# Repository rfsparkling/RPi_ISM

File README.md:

# RPi ISM — open sub-GHz radio HATs for Raspberry Pi

<p align="center"><sub>RPi ISM v1 (rev 0V3) on a Raspberry Pi 3 Model B with an 868 MHz antenna on the vertical SMA. HAT rendered from the PCB data (work-in-progress layout); the Raspberry Pi is a simplified mechanical mock-up.</sub></p>

**RPi ISM** is a family of fully open radio add-on boards for the Raspberry Pi.
Hardware, firmware and software are all open source. The goal: turn any
Raspberry Pi into a capable, well-engineered sub-GHz ISM gateway, sensor hub
and RF lab tool, without proprietary hubs or closed binary stacks.

The mechanical concept, a cross-PCB receptacle that sits directly on the
Raspberry Pi GPIO header, comes from the author's
[QRPi WSPR transmitter](https://web.tapr.org/meetings/DCC_2015/DCC2015-QRPi-HA7DCD-1.pdf)
(HA7DCD), used on the Raspberry Pi 1 and 2 and produced in thousands of units
by [TAPR](https://tapr.org/product/wspr/).

<p align="center"><sub>QRPi on a Raspberry Pi 1 Model B: cross-PCB receptacle on the GPIO header, board cut-out clearing the DSI (S2) connector.</sub></p>

The first member of the family, **RPi ISM v1**, is built around the Silicon Labs
**Si4463** transceiver for the **863–870 MHz (SRD 868)** band. More families
with newer radio chips are planned (see [Product family](#product-family)).

> **Status:** early development. The v1 schematic (rev 0V3) is near-final;
> the PCB layout is being completed and migrated from Eagle to KiCad.
> The software stack is being designed. Not ready for production use yet.

---

## What is it good for?

RPi ISM v1 is an **(G)FSK / OOK** radio. It does *not* speak Zigbee, Thread or
other 2.4 GHz 802.15.4 protocols. It targets the things a cheap 2.4 GHz
dongle cannot do:

| Use case | Who | Notes |
|---|---|---|
| **Wireless M-Bus / OMS meter reading** (EN 13757-4, S1/T1/C1 modes) | Utilities, building management, home users | Water, heat, gas meters and heat-cost allocators. Planned as a [wmbusmeters](https://github.com/wmbusmeters/wmbusmeters) backend, with transmit capability. |
| **868 MHz home automation** | Home Assistant / FHEM / openHAB users | KNX-RF, eQ-3 MAX!, Homematic (classic) and other 868 MHz FSK systems. |
| **Long-range telemetry** | Industrial, agriculture, off-grid | Up to +20 dBm; the 869.40–869.65 MHz sub-band allows 500 mW ERP at 10 % duty cycle. Reaches outbuildings and basements where 2.4 GHz meshes struggle. |
| **RF pre-compliance and lab tool** | Hardware developers, test labs | CW and PN9 test signals, RSSI sweep, band occupancy and duty-cycle monitoring, LBT testing for ETSI EN 300 220. |
| **6LoWPAN / IPv6 over sub-GHz** | Researchers, makers | Through a planned Linux `mac802154` driver (802.15.4g SUN-FSK PHY). |

---

## Hardware — RPi ISM v1 (rev 0V3)

| Item | Part | Notes |
|---|---|---|
| Transceiver | Silicon Labs **Si4463-B1B-FMR** | 119–1050 MHz, (G)FSK/4(G)FSK/OOK, up to +20 dBm. [Datasheet](https://www.silabs.com/documents/public/data-sheets/Si4464-63-61-60.pdf). Moving to **Si4463-C2A** in the next revision. |
| RF filter | TDK/EPCOS **B39871B3725U410** SAW | 869 MHz. This filter fixes the board to the 868 MHz SRD band. [Datasheet](http://www.mouser.com/ds/2/400/B3725-525464.pdf) |
| RF switch | CEL **UPG2214TB-A** | TX/RX switching. [Datasheet](http://www.cel.com/pdf/datasheets/upg2214tb.pdf) |
| Reference | Kyocera **KT2520F26000ACW18TAN** TCXO | 26 MHz. [Datasheet](http://www.mouser.com/ds/2/40/kt2520_gps_e_2012-838160.pdf) |
| Antenna port | Vertical SMA (SMA1) | Population option; 50 Ω |
| Host interface | SPI + GPIO IRQ | 2×15 receptacle (Samtec CLH-115), mates with pins 1–30 of the Raspberry Pi GPIO header (SPI0 included) |
| Extras | Buzzer (BC817 driver), status LEDs | |
| PCB | 2 layers, 45.1 × 34.1 mm | |

Design files are in [`CAD/`](CAD/) (Eagle 6.4, with PDF exports of the
schematic and both copper layers).

### Known issues in rev 0V3

- PCB layout is not finished yet (unrouted nets, components outside the board outline).
- Missing flyback diode across the inductive buzzer load on the BC817 collector.
- TCXO `VC` pin floats through SJ7 (fine for the non-VC KT2520 variant only).
- The matching network is tuned for 868 MHz; other bands need new values.
- The SAW filter and the RF switch are not stocked at LCSC (relevant for JLCPCB assembly).
- The board cut-out (for the display flex) has one distorted corner arc: the top
  edge ends at x = 40.42 mm instead of 40.17 mm.

### Planned for the next revision

- KiCad migration, finished layout, JLCPCB-ready fabrication and assembly files (Gerber, BOM, CPL).
- **Band variants** via BOM options: 433 MHz, 868 MHz, 915 MHz (SAW filter and matching network change).
- Si4463-C2A silicon, the fixes listed above.

---

## Software stack (planned)

```
┌──────────────────────────────────────────────────────────────┐
│ Applications: Home Assistant · MQTT · wmbusmeters · FHEM      │
├───────────────┬──────────────────┬───────────────────────────┤
│ wM-Bus backend│ si446x-cli tools │ Linux mac802154 driver     │
│ (S/T/C modes) │ CW·PN9·RSSI scan │ → 6LoWPAN / IPv6 (wpan)    │
├───────────────┴──────────────────┴───────────────────────────┤
│ libsi446x — portable C driver (clean-room, permissive license)│
├──────────────────────────────────────────────────────────────┤
│ Linux backend: spidev + libgpiod v2  │ HAL for Zephyr / bare  │
└──────────────────────────────────────────────────────────────┘
```

1. **libsi446x** — a clean-room driver written from Silicon Labs' public API
   documentation (AN625). Portable HAL; the first backend is Linux userspace
   (`spidev` + `libgpiod`).
2. **si446x-cli** — test and bring-up tool: CW / PN9 transmit, RSSI sweep,
   packet TX/RX, band occupancy and duty-cycle logging.
3. **Wireless M-Bus** — S1/T1/C1 reception and transmission, with 3-of-6 and
   Manchester decoding in software, integrated as a wmbusmeters backend.
4. **Linux `mac802154` driver** — native 802.15.4g SUN-FSK support for
   `wpan-tools` and 6LoWPAN, aimed at upstream inclusion.
5. **Stretch goals** — DASH7 (reusing the Si4460 PHY driver of the
   Apache-2.0 [Sub-IoT / OSS-7](https://github.com/CoSys-Lab/dash7-ap-open-source-stack)
   stack); a Wi-SUN radio co-processor compatible with Silicon Labs'
   [wisun-br-linux](https://github.com/SiliconLabs/wisun-br-linux) border router.

**Timing note:** at 100 kbps (wM-Bus C1) the 64-byte FIFO (129 bytes when
merged) fills in about 5–10 ms, which a userspace IRQ handler can serve.
Long T1 telegrams and 6LoWPAN at higher rates are better served by the
kernel driver or a PREEMPT_RT kernel.

---

## Product family

RPi ISM v1 is the first board of a family. The shared parts — the
Raspberry Pi mechanical and electrical interface, the Linux integration,
the test tools and the open, clean-room software policy — carry over to
every member. Each new board adds a radio.

| Family | Radio | Bands / protocols | Status |
|---|---|---|---|
| **RPi ISM v1** | Si4463 | Sub-GHz (G)FSK/OOK: wM-Bus, KNX-RF, proprietary FSK, 802.15.4g | Layout in progress |
| **[ionos-maximus](https://github.com/ionos-sdr/ionos-maximus-rpi-sdr)** | EFR32FG23 (Silabs radio board BRD4265B) | Sub-GHz packet modem **and** I/Q streaming to the Pi (target ~1 Msps) | Routed, first board to be completed |
| Next generations | Newer sub-GHz and multi-protocol radios | Candidates: LoRa + FSK, Wi-SUN-class sub-GHz, dual-radio boards adding 2.4 GHz (Zigbee / Thread RCP) next to sub-GHz | Planned |

Where the family is most useful in industry, and how that sets the software
roadmap: [docs/industrial-use-cases.md](docs/industrial-use-cases.md).

Chip selection for the next families is open. Suggestions and use cases are
welcome in the issues.

---

## Licensing and clean-room policy

- **Hardware** (schematics, layouts, fabrication files, 3D and mechanical
  files): [**CERN-OHL-S-2.0**](LICENSES/CERN-OHL-S-2.0.txt).
- **Software and firmware** (drivers, libraries, tools):
  [**Apache-2.0**](LICENSES/Apache-2.0.txt), so the driver can be built into
  commercial products as well.
- Details in [`LICENSE`](LICENSE). Earlier revisions were published under the
  GPL v3 and remain available under it.
- **No code under the Silicon Labs Master Software License Agreement (MSLA)
  is included.** The MSLA is the default license of the Gecko SDK and is
  not an open source license.
- Silicon Labs files that are explicitly marked **Zlib** in their header may
  be reused, with the license notice kept and modifications clearly marked.
- Radio configurations are written from the public datasheet and API
  documentation. Binary ROM patches are not redistributed.
- Third-party code with copyleft licenses (for example RadioHead, GPL) is
  only used where license compatibility is confirmed.

---

## Repository layout

```
CAD/         Eagle design files (schematic, board) and PDF exports — rev 0V3
datasheet/   Links to component datasheets and Raspberry Pi interfacing docs
docs/img/    Renders and photos
LICENSES/    Full license texts (CERN-OHL-S-2.0, Apache-2.0)
RPism_buzzer_crossreference_file.xlsx   Raspberry Pi J8 ↔ radio pin mapping
top.png      Layout preview
```

KiCad sources, firmware and software directories will be added as the work
progresses.

---

## Contributing

Issues and pull requests are welcome: hardware review, protocol support,
band variants and real-world test results are all valuable. For larger
changes, open an issue first to discuss the approach.

Developed by **RF Sparkling Kft.** (Budapest / Veszprém, Hungary).

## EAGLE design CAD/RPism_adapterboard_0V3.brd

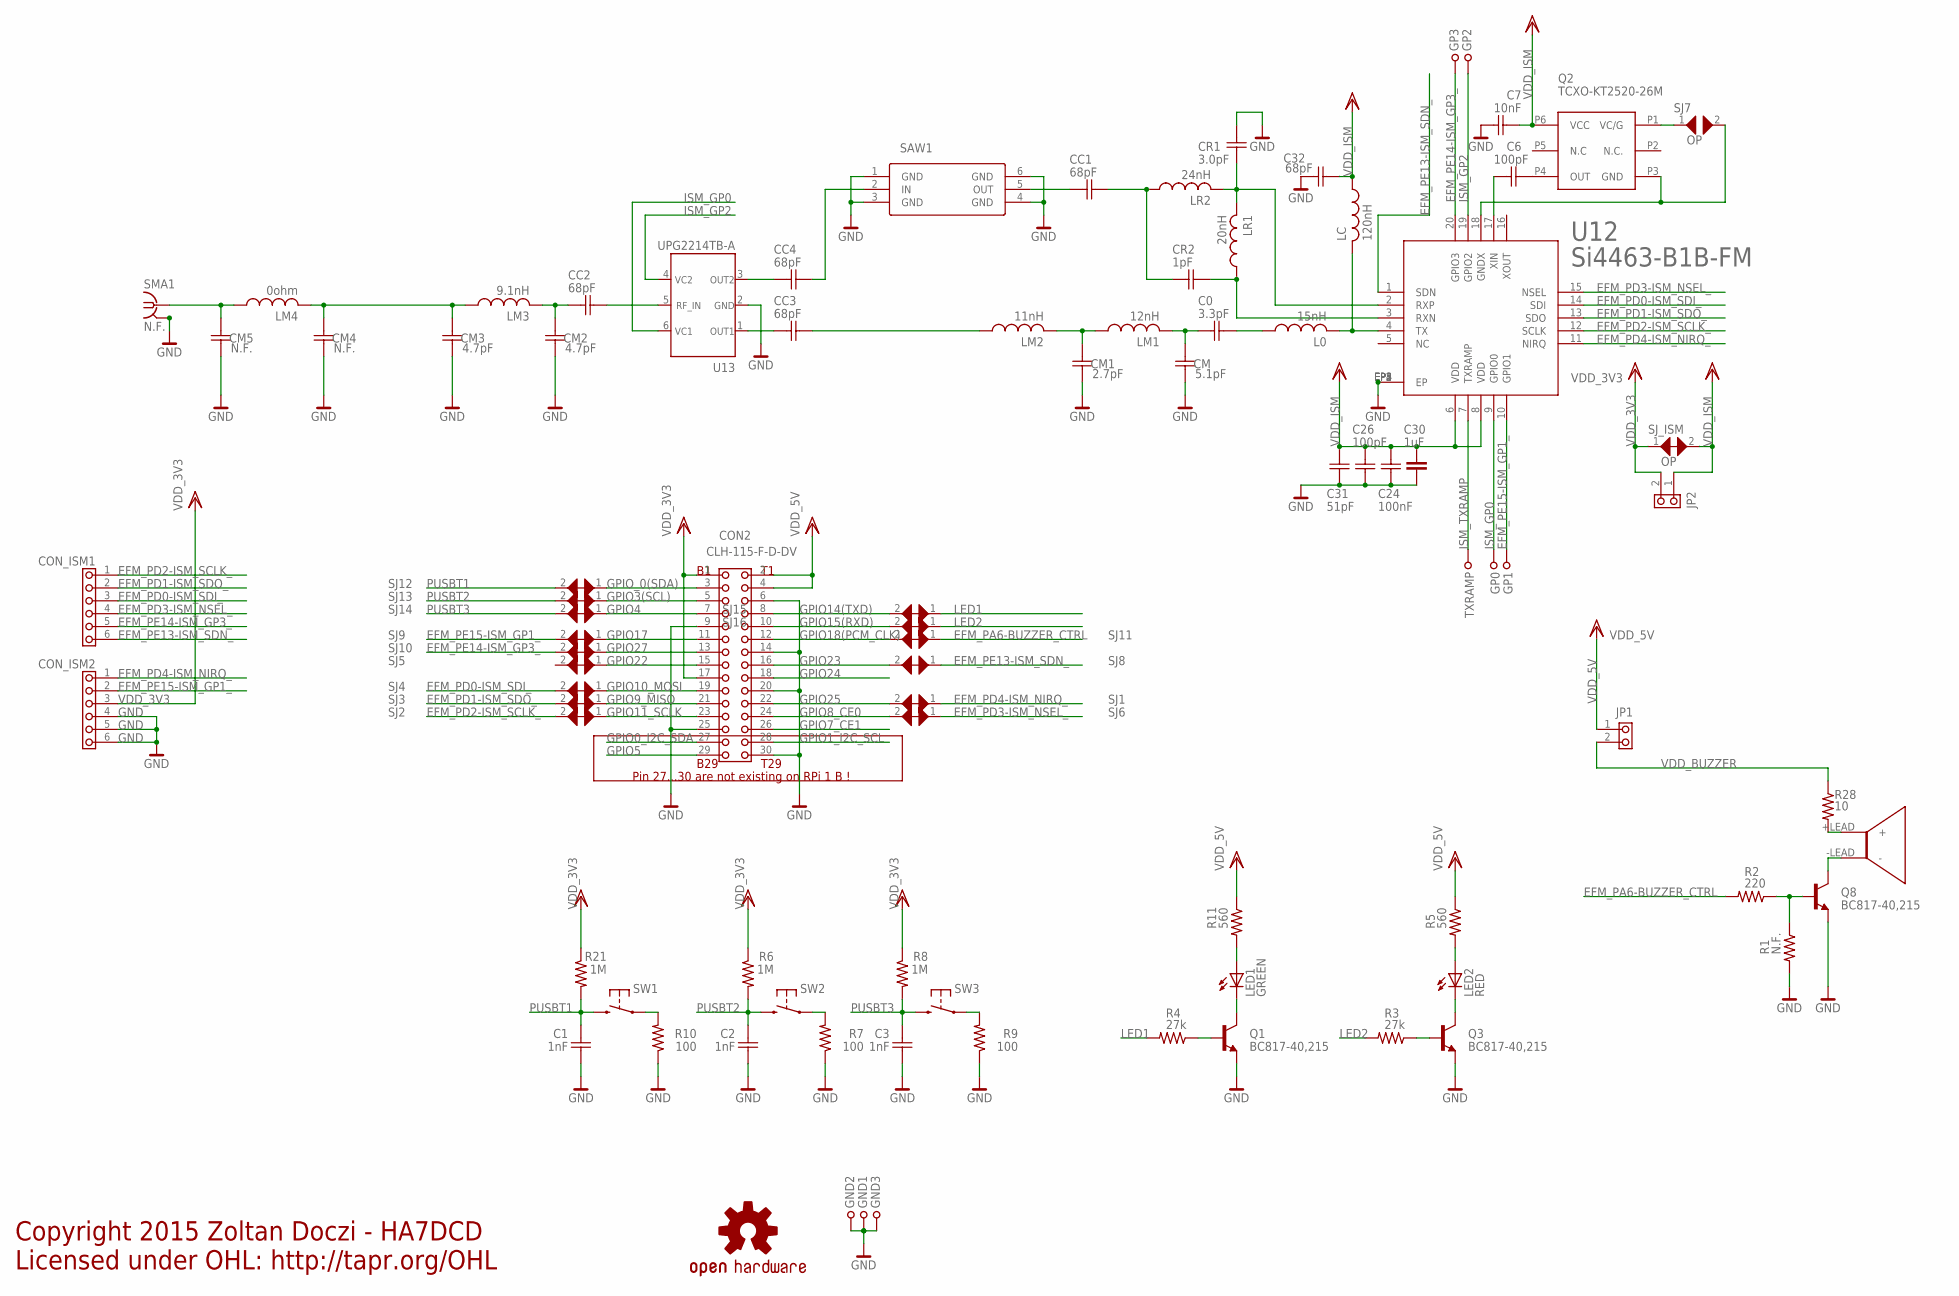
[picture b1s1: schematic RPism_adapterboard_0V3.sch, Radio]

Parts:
BUZZ1: SMT-0540-S-R
C0: 3.3pF; CAPC1005X60N
C1, C2, C3: 1nF; CAPC1005X60N
C6, C26: 100pF; CAPC1005X60N
C7: 10nF; CAPC1005X60N
C24: 100nF; CAPC1005X60N
C30: 1uF; 0603
C31: 51pF; CAPC1005X60N
C32: 68pF; CAPC1005X60N
CC1, CC2, CC3, CC4: 68pF; CAPC1005X60N
CM: 5.1pF; CAPC1005X60N
CM1: 2.7pF; CAPC1005X60N
CM2, CM3: 4.7pF; CAPC1005X60N
CM4, CM5: N.F.; CAPC1005X60N
CON2: CLH-115-F-D-DV; 2X15_SMT_CROSSPCB_ASSYM
CON_ISM1: MALE__PIN6S-2MM; PIN6S_2MM
CON_ISM2: FEMALE__PIN6S-2MM; PIN6S_2MM
CR1: 3.0pF; CAPC1005X60N
CR2: 1pF; CAPC1005X60N
GND1, GND2, GND3: TESTPOINT39MIL; TESTPOINT1,0
GP0, GP1, GP2, GP3: TESTPOINT20MIL; TESTPOINT0,5
JP1: JUMPER2; PIN2-1R
JP2: N.F.; PIN2-1R
L0: 15nH; 0402-INDUCT; PARTNR LQW15AN15NJ00
LC: 120nH; 0402-INDUCT; PARTNR LQW15ANR12J00
LED1: GREEN; LED-0603
LED2: RED; LED-0603
LM1: 12nH; 0402-INDUCT; PARTNR LQW15AN12NJ00
LM2: 11nH; 0402-INDUCT; PARTNR LQW15AN11NJ00
LM3: 9.1nH; 0402-INDUCT; PARTNR LQW15AN9N1J00
LM4: 0ohm; 0402-INDUCT; PARTNR LQW15AN12NJ00
LR1: 20nH; 0402-INDUCT; PARTNR LQW15AN20NJ00D
LR2: 24nH; 0402-INDUCT; PARTNR LQW15AN24NJ00D
Q1, Q3, Q8: BC817-40,215; SOT23-BEC
Q2: TCXO-KT2520-26M; TCXO_2.5X2MM
R1: N.F.; R0402
R2: 220; R0402
R3, R4: 27k; R0402
R5, R11: 560; R0402
R6, R8, R21: 1M; R0402
R7, R9, R10: 100; R0402
R28: 10; R0402
SAW1: SAW_EPCOS_B3725; DCC6C
SJ1, SJ2, SJ3, SJ4, SJ5, SJ6, SJ8, SJ9, SJ10, SJ11, SJ12, SJ13, SJ14, SJ15, SJ16: JUMPER_SMD_MICRO_SHORT
SJ7: OP; JUMPER_SMD_MICRO
SJ_ISM: OP; JUMPER_SMD_MICRO_SHORT
SMA1: N.F.; BU-SMA-V
SW1, SW2, SW3: DTSM_32N
TXRAMP: TESTPOINT20MIL; TESTPOINT0,5
U12: Si4463-B1B-FM; QFN-20_PRO2_VERIFIED
U13: UPG2214TB-A; 6-PIN_SUPER_MINIMOLD
U$15: OSHW-LOGOL; OSHW-LOGO-L

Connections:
EFM_PA6-BUZZER_CTRL: R2.2, SJ11.1
EFM_PD0-ISM_SDI_: CON_ISM1.3, SJ4.2, U12.14 (SDI)
EFM_PD1-ISM_SDO_: CON_ISM1.2, SJ3.2, U12.13 (SDO)
EFM_PD2-ISM_SCLK_: CON_ISM1.1, SJ2.2, U12.12 (SCLK)
EFM_PD3-ISM_NSEL_: CON_ISM1.4, SJ6.1, U12.15 (NSEL)
EFM_PD4-ISM_NIRQ_: CON_ISM2.1, SJ1.1, U12.11 (NIRQ)
EFM_PE13-ISM_SDN_: CON_ISM1.6, SJ8.1, U12.1 (SDN)
EFM_PE14-ISM_GP3_: CON_ISM1.5, GP3.1, SJ10.2, U12.20 (GPIO3)
EFM_PE15-ISM_GP1_: CON_ISM2.2, GP1.1, SJ9.2, U12.10 (GPIO1)
GND: C1.2 (C2), C2.2 (C2), C3.2 (C2), C7.1 (C1), C24.2 (C2), C26.2 (C2), C30.1, C31.2 (C2), C32.1 (C1), CM.2 (C2), CM1.2 (C2), CM2.2 (C2), CM3.2 (C2), CM4.2 (C2), CM5.2 (C2), CON2.6, CON2.9, CON2.14, CON2.20, CON2.25, CON2.30, CON_ISM2.4, CON_ISM2.5, CON_ISM2.6, CR1.1 (C1), GND1.1, GND2.1, GND3.1, Q1.E, Q3.E, Q8.E, R1.2, R7.1, R9.1, R10.1, SAW1.1 (GND), SAW1.3 (GND), SAW1.4 (GND), SAW1.6 (GND), SMA1.2, SMA1.3, SMA1.4, SMA1.5, U12.EP0 (EP), U12.EP1 (EP), U12.EP2 (EP), U12.EP3 (EP), U12.EP4 (EP), U12.EP5 (EP), U13.2
GPIO0_I2C_SDA: CON2.27
GPIO1_I2C_SCL: CON2.28
GPIO3(SCL): CON2.5, SJ13.1
GPIO4: CON2.7, SJ14.1
GPIO5: CON2.29
GPIO7_CE1: CON2.26
GPIO8_CE0: CON2.24, SJ6.2
GPIO9_MISO: CON2.21, SJ3.1
GPIO10_MOSI: CON2.19, SJ4.1
GPIO11_SCLK: CON2.23, SJ2.1
GPIO14(TXD): CON2.8, SJ15.2
GPIO15(RXD): CON2.10, SJ16.2
GPIO17: CON2.11, SJ9.1
GPIO18(PCM_CLK): CON2.12, SJ11.2
GPIO22: CON2.15, SJ5.1
GPIO23: CON2.16, SJ8.2
GPIO24: CON2.18
GPIO25: CON2.22, SJ1.2
GPIO27: CON2.13, SJ10.1
GPIO_0(SDA): CON2.3, SJ12.1
ISM_GP0: GP0.1, U12.9 (GPIO0), U13.6
ISM_GP2: GP2.1, U12.19 (GPIO2), U13.4
ISM_TXRAMP: TXRAMP.1, U12.7 (TXRAMP)
LED1: R4.2, SJ15.1
LED2: R3.2, SJ16.1
unnamed: Q1.B, R4.1
unnamed: LED1.C, Q1.C
unnamed: LED1.A, R11.2
unnamed: LED2.C, Q3.C
unnamed: LED2.A, R5.2
unnamed: Q3.B, R3.1
unnamed: R7.2, SW2.1
unnamed: C6.1 (C1), U12.17 (XIN)
unnamed: R9.2, SW3.1
unnamed: C6.2 (C2), Q2.P4 (OUT)
unnamed: R10.2, SW1.1
unnamed: BUZZ1.+LEAD (+), R28.2
unnamed: BUZZ1.-LEAD (-), Q8.C
unnamed: Q8.B, R1.1, R2.1
unnamed: CC1.1 (C1), SAW1.5 (OUT)
unnamed: Q2.P1 (VC/G), SJ7.1
unnamed: L0.2, LC.2, U12.4 (TX)
unnamed: C0.1 (C1), L0.1
unnamed: C0.2 (C2), CM.1 (C1), LM1.2
unnamed: CM1.1 (C1), LM1.1, LM2.2
unnamed: CC3.2 (C2), LM2.1
unnamed: CC3.1 (C1), U13.1
unnamed: CC2.2 (C2), U13.5
unnamed: CR2.1 (C1), LR1.1, U12.3 (RXN)
unnamed: CR1.2 (C2), LR1.2, LR2.2, U12.2 (RXP)
unnamed: Q2.P3 (GND), SJ7.2, U12.18 (GNDX)
unnamed: CC1.2 (C2), CR2.2 (C2), LR2.1
unnamed: CC4.2 (C2), SAW1.2 (IN)
unnamed: CC4.1 (C1), U13.3
PUSBT1: C1.1 (C1), R21.2, SJ12.2, SW1.2
PUSBT2: C2.1 (C1), R6.2, SJ13.2, SW2.2
PUSBT3: C3.1 (C1), R8.2, SJ14.2, SW3.2
RF3: CM5.1 (C1), LM4.1, SMA1.1
RF10: CC2.1 (C1), CM2.1 (C1), LM3.2
RF12: CM3.1 (C1), CM4.1 (C1), LM3.1, LM4.2
VDD_3V3: CON2.1, CON2.17, CON_ISM2.3, JP2.2 (B), R6.1, R8.1, R21.1, SJ_ISM.1
VDD_5V: CON2.2, CON2.4, JP1.1 (A), R5.1, R11.1
VDD_BUZZER: JP1.2 (B), R28.1
VDD_ISM: C7.2 (C2), C24.1 (C1), C26.1 (C1), C30.2, C31.1 (C1), C32.2 (C2), JP2.1 (A), LC.1, Q2.P6 (VCC), SJ_ISM.2, U12.6 (VDD), U12.8 (VDD)

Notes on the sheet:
Copyright 2015 Zoltan Doczi - HA7DCD Licensed under OHL: http://tapr.org/OHL
Pin 27...30 are not existing on RPi 1 B !

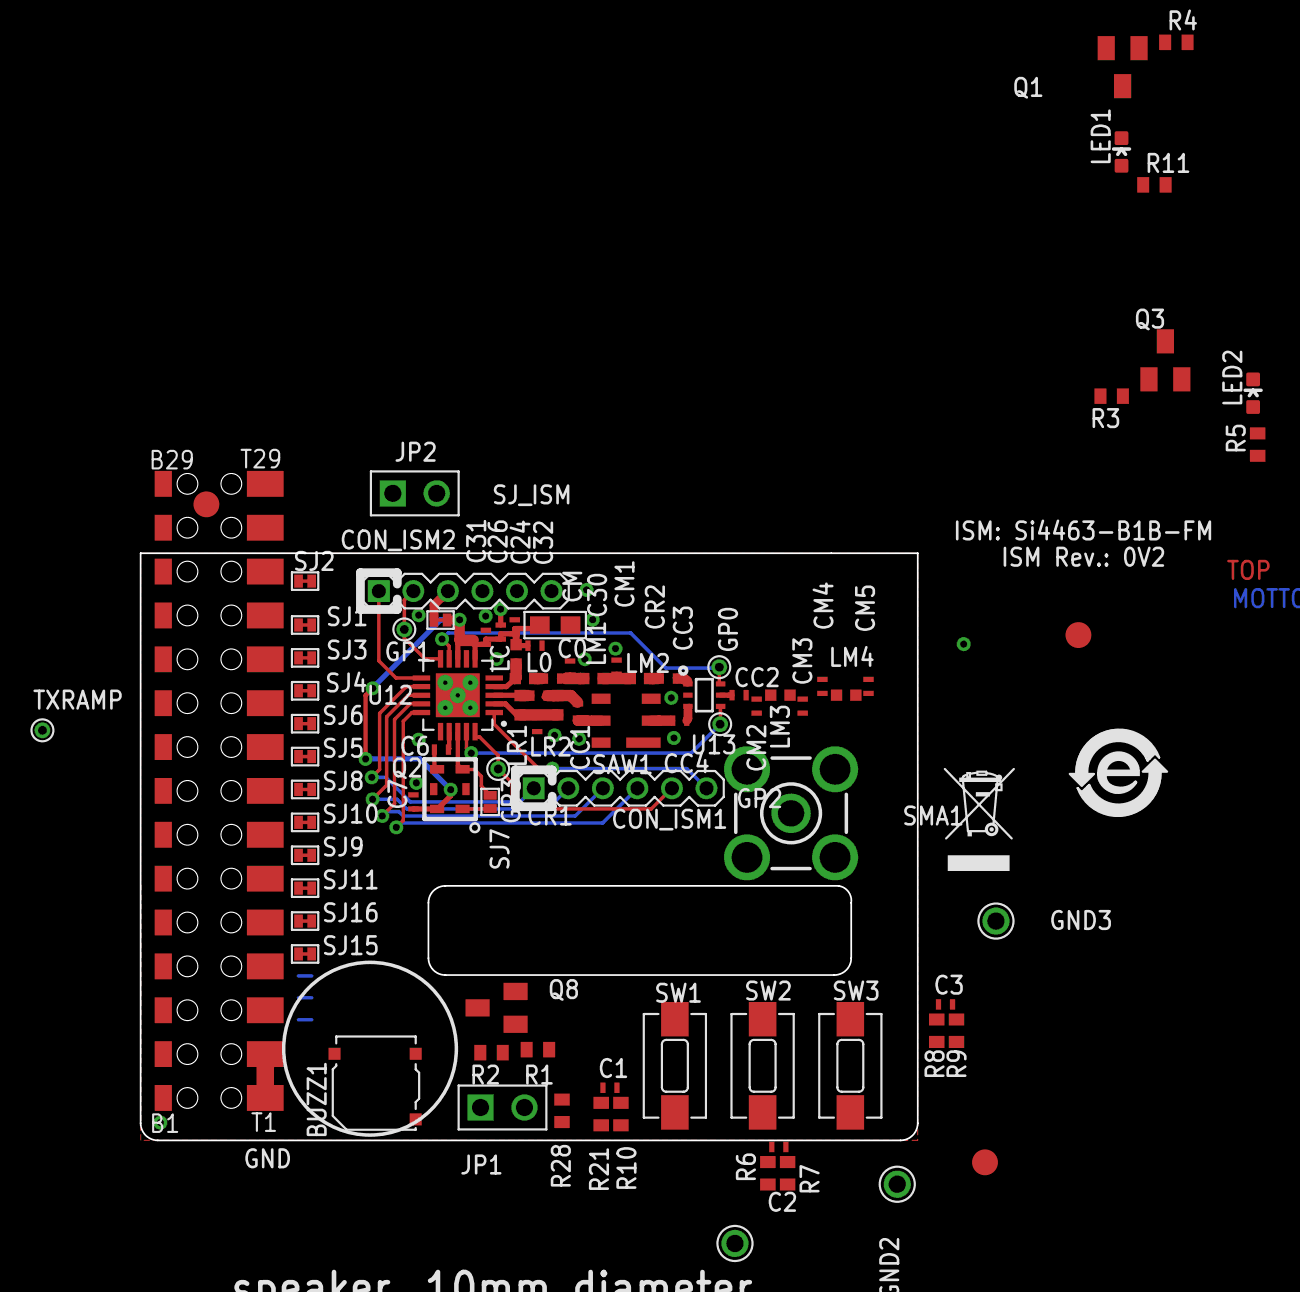
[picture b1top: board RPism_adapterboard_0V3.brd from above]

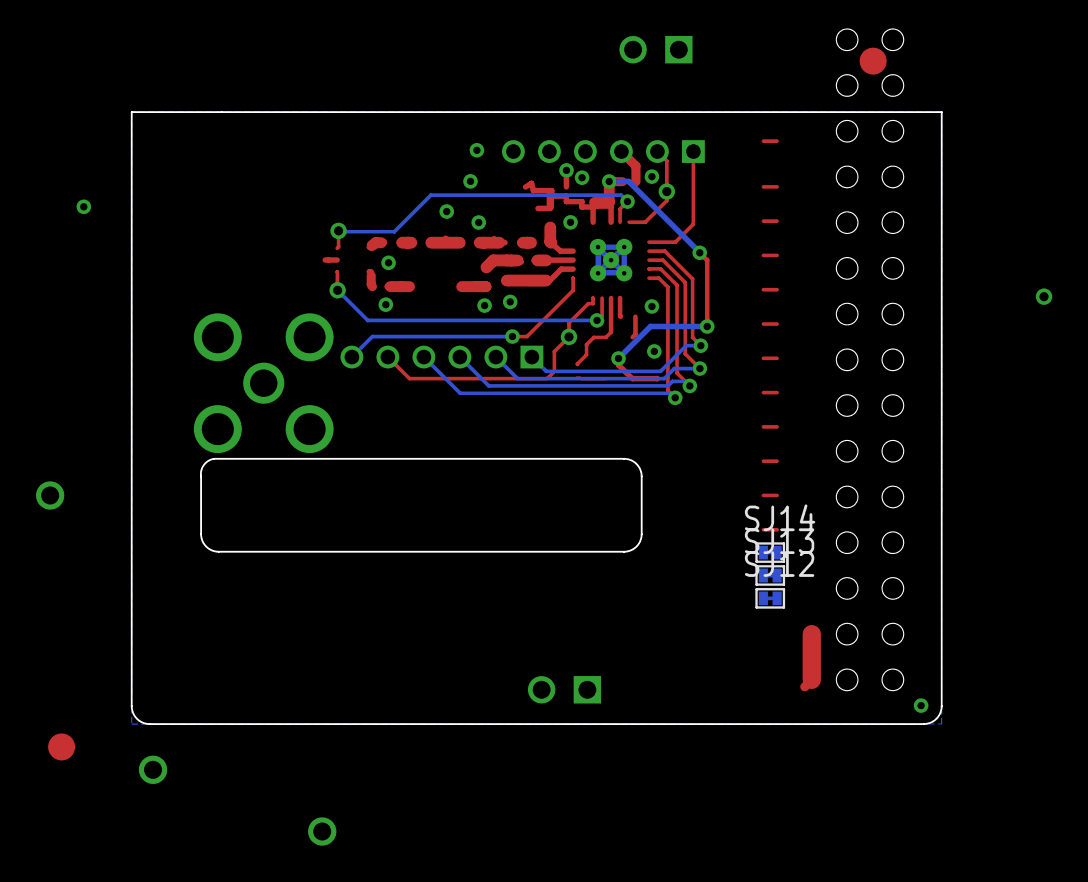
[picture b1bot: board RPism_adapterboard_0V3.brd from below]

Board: 2 copper layers, 45.0 x 34.0 mm, 94 parts (3 on the bottom side), 69 nets.

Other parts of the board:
U$1, U$115, U$116: FIDUCIAL
U$142: NON-DISPOSABLE
U$143: ROHS_CHINA

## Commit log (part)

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2017-02-24 uploading 90% ready cad files + datasheets
2017-02-24 formatting
